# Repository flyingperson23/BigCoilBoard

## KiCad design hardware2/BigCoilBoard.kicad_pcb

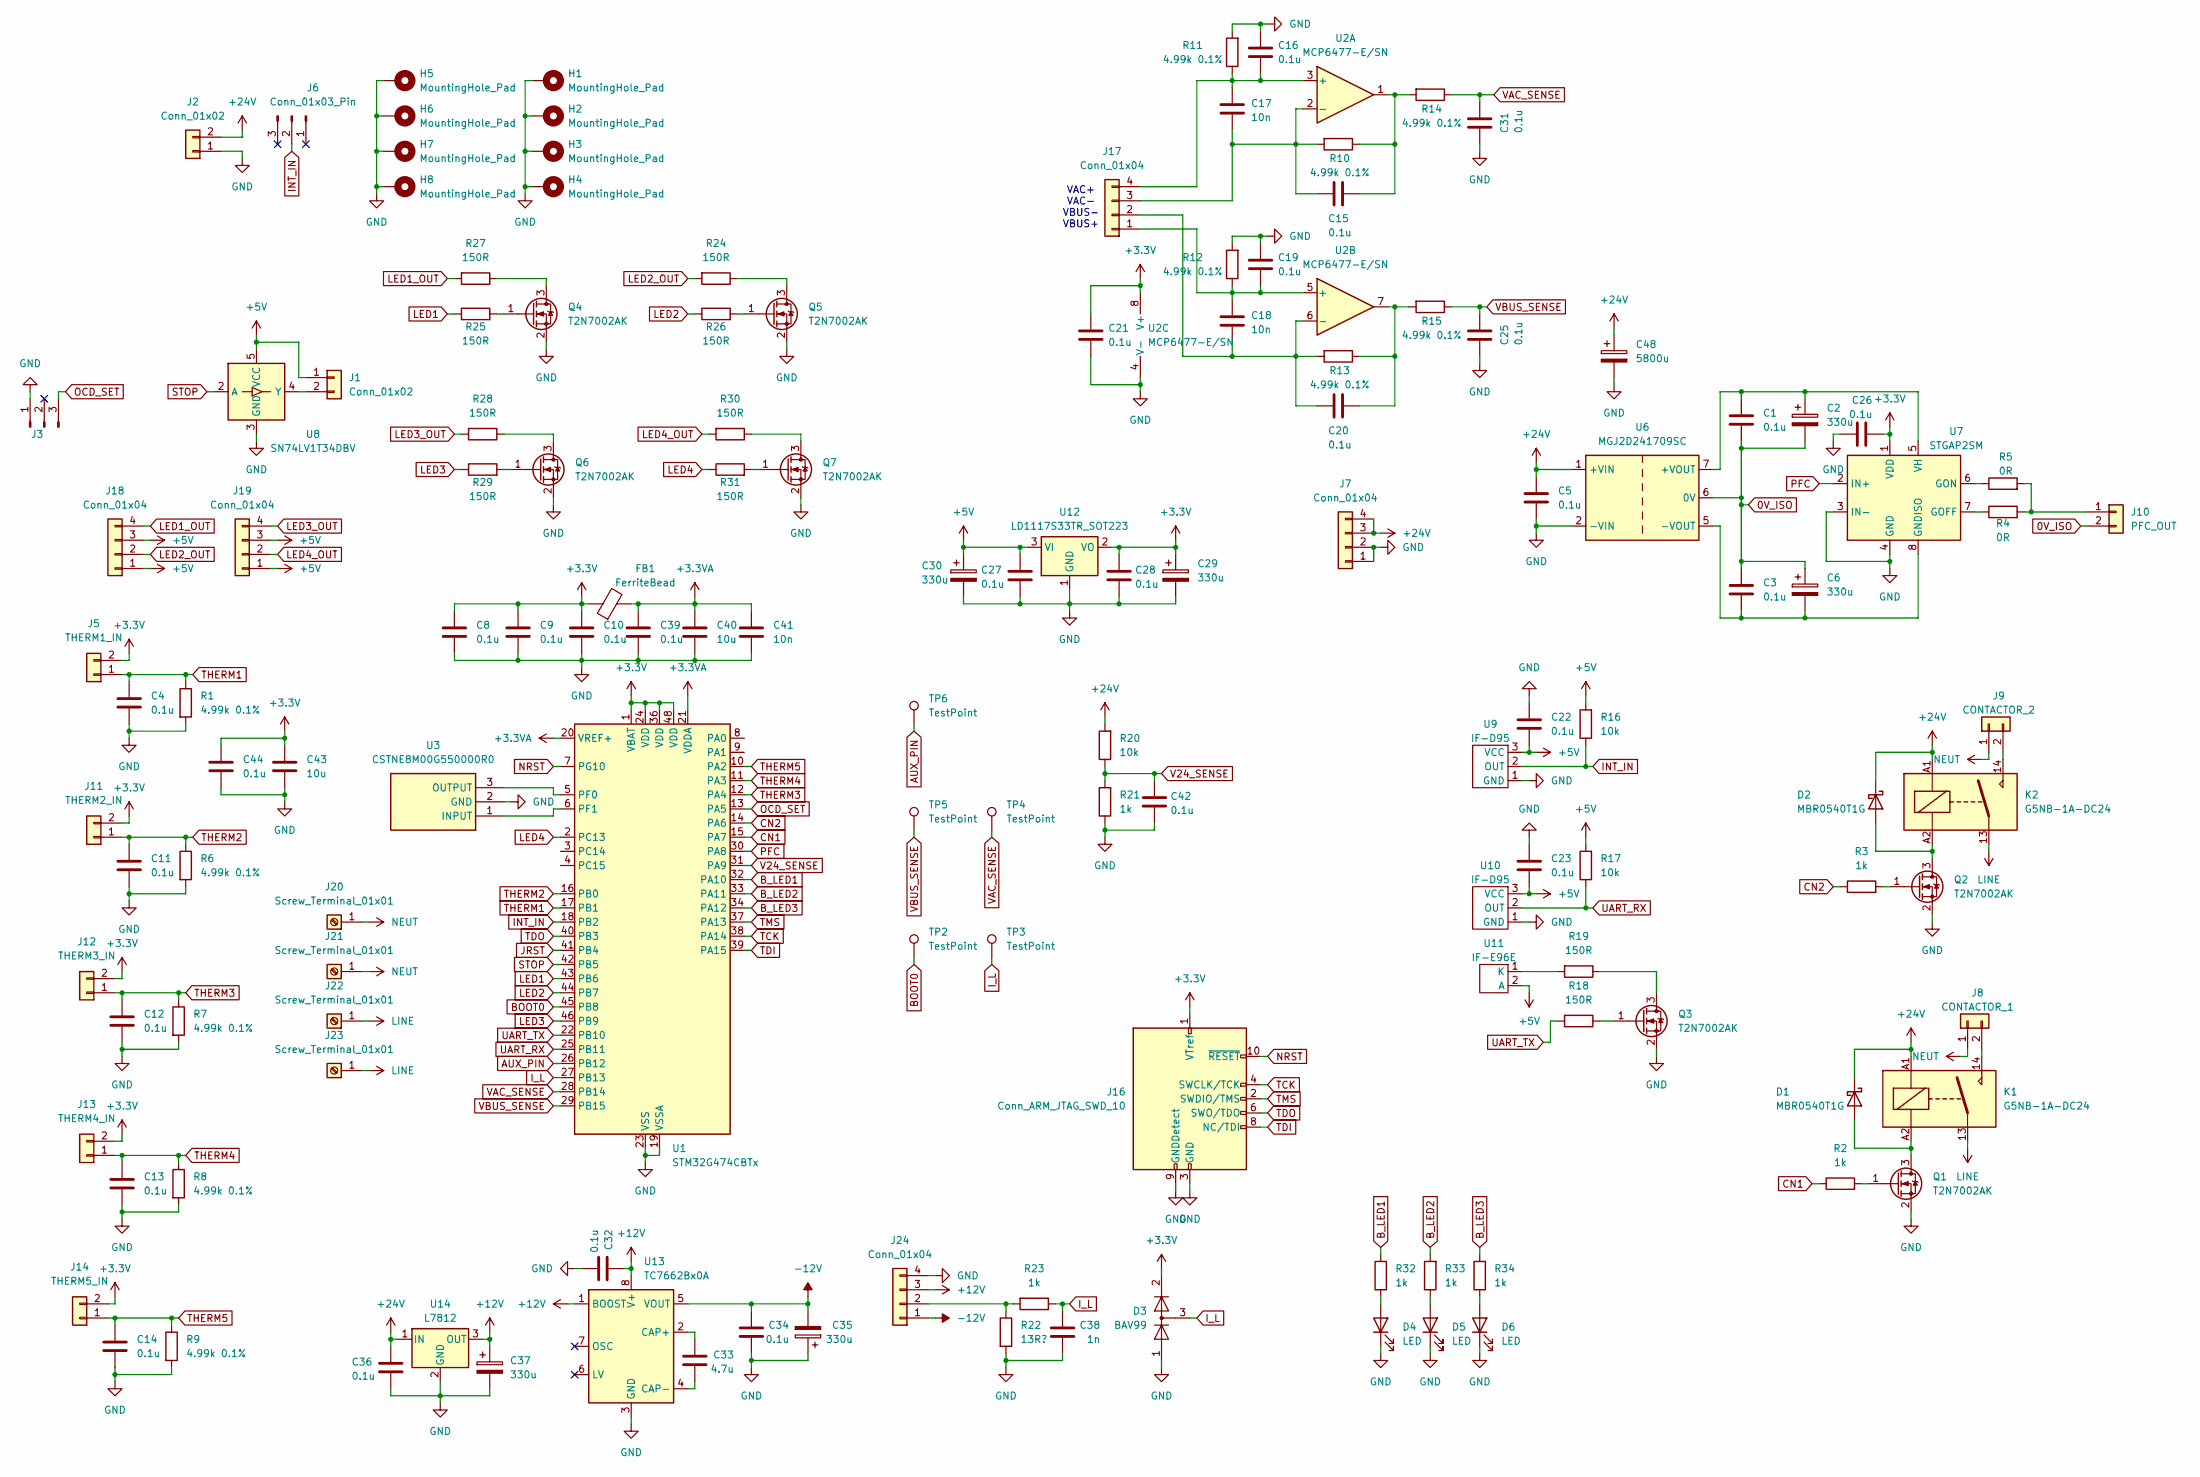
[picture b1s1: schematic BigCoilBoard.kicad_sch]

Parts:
C1, C3, C4, C5, C8, C9, C10, C11, C12, C13, C14, C15, C16, C19, C20, C21, C22, C23, C25, C26, C27, C28, C31, C32, C34, C36, C39, C42, C44: 0.1u; C_0805_2012Metric
C2, C6, C29, C30, C35, C37: 330u; 860020575013
C17, C18, C41: 10n; C_0805_2012Metric
C33: 4.7u; C_0805_2012Metric
C38: 1n; C_0805_2012Metric
C40, C43: 10u; C_0805_2012Metric
C48: 5800u; 860010581026
D1, D2: MBR0540T1G; D_SOD-123
D3: BAV99; SOT-23
D4, D5, D6: LED; LED_0805_2012Metric
FB1: FerriteBead; L_1206_3216Metric
H1, H2, H3, H4: MountingHole_Pad; MountingHole_2.7mm_M2.5_Pad_Via
H5, H6, H7, H8: MountingHole_Pad; MountingHole_4.3mm_M4_Pad_Via
J1, J2: Conn_01x02; PinSocket_1x02_P2.54mm_Vertical
J3, J6: Conn_01x03_Pin; PinSocket_1x03_P2.54mm_Vertical
J5: THERM1_IN; Molex_KK-254_AE-6410-02A_1x02_P2.54mm_Vertical
J7, J17, J18, J19, J24: Conn_01x04; Molex_KK-254_AE-6410-04A_1x04_P2.54mm_Vertical
J8: CONTACTOR_1; Molex_KK-254_AE-6410-02A_1x02_P2.54mm_Vertical
J9: CONTACTOR_2; Molex_KK-254_AE-6410-02A_1x02_P2.54mm_Vertical
J10: PFC_OUT; Molex_KK-254_AE-6410-02A_1x02_P2.54mm_Vertical
J11: THERM2_IN; Molex_KK-254_AE-6410-02A_1x02_P2.54mm_Vertical
J12: THERM3_IN; Molex_KK-254_AE-6410-02A_1x02_P2.54mm_Vertical
J13: THERM4_IN; Molex_KK-254_AE-6410-02A_1x02_P2.54mm_Vertical
J14: THERM5_IN; Molex_KK-254_AE-6410-02A_1x02_P2.54mm_Vertical
J16: Conn_ARM_JTAG_SWD_10; PinHeader_2x05_P1.27mm_Vertical
J20, J21, J22, J23: Screw_Terminal_01x01; Wuerth_REDCUBE-THR_WP-THRBU_74650074_THR
K1, K2: G5NB-1A-DC24; Relay_SPST_Omron_G5NB
Q1, Q2, Q3, Q4, Q5, Q6, Q7: T2N7002AK; SOT-23
R1, R6, R7, R8, R9, R10, R11, R12, R13, R14, R15: 4.99k 0.1%; R_0805_2012Metric
R2, R3, R21, R23, R32, R33, R34: 1k; R_0805_2012Metric
R4, R5: 0R; R_1210_3225Metric
R16, R17, R20: 10k; R_0805_2012Metric
R18, R19, R24, R25, R26, R27, R28, R29, R30, R31: 150R; R_0805_2012Metric
R22: 13R?; R_Axial_DIN0207_L6.3mm_D2.5mm_P10.16mm_Horizontal
TP2, TP3, TP4, TP5, TP6: TestPoint; TestPoint_Pad_2.0x2.0mm
U1: STM32G474CBTx; LQFP-48_7x7mm_P0.5mm
U2: MCP6477-E/SN; SOIC-8_3.9x4.9mm_P1.27mm
U3: CSTNE8M00G550000R0; Resonator_SMD_Murata_CSTxExxV-3Pin_3.0x1.1mm; Mouser Part Number 81-CSTNE8M00G550000R
U6: MGJ2D241709SC; Converter_DCDC_Murata_MGJ2DxxxxxxSC_THT
U7: STGAP2SM; SOIC-8_3.9x4.9mm_P1.27mm
U8: SN74LV1T34DBV; SOT-23-5
U9, U10: IF-D95
U11: IF-E96E
U12: LD1117S33TR_SOT223; SOT-223-3_TabPin2
U13: TC7662Bx0A; SOIC-8_3.9x4.9mm_P1.27mm
U14: L7812; TO-220-3_Vertical

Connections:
0V_ISO: C1.2, C2.2, C3.1, C6.1, J10.2, U6.6 (0V)
+3.3V: C8.1, C9.1, C10.1, C21.1, C26.2, C28.1, C29.1, C43.1, C44.1, D3.2 (A), FB1.1, J5.2, J11.2, J12.2, J13.2, J14.2, J16.1 (VTref), U1.1 (VBAT), U1.24 (VDD), U1.36 (VDD), U1.48 (VDD), U2.8 (V+), U7.1 (VDD), U12.2 (VO)
+3.3VA: C39.1, C40.1, C41.1, FB1.2, U1.20 (VREF+), U1.21 (VDDA)
+5V: C22.2, C23.2, C27.1, C30.1, J1.1, J18.1, J18.3, J19.1, J19.3, R16.2, R17.2, U8.5 (VCC), U9.3 (VCC), U10.3 (VCC), U11.2 (A), U12.3 (VI)
+12V: C32.1, C37.1, J24.3, U13.1 (BOOST), U13.8 (V+), U14.3 (OUT)
+24V: C5.1, C36.1, C48.1, D1.1 (K), D2.1 (K), J2.2, J7.3, J7.4, K1.A1, K2.A1, R20.2, U6.1 (+VIN), U14.1 (IN)
-12V: C34.2, C35.2, J24.1, U13.5 (VOUT)
AUX_PIN: TP6.1, U1.26 (PB12)
BOOT0: TP2.1, U1.45 (PB8)
B_LED1: R32.2, U1.32 (PA10)
B_LED2: R33.2, U1.33 (PA11)
B_LED3: R34.2, U1.34 (PA12)
CN1: R2.1, U1.15 (PA7)
CN2: R3.1, U1.14 (PA6)
GND: C4.2, C5.2, C8.2, C9.2, C10.2, C11.2, C12.2, C13.2, C14.2, C16.1, C19.1, C21.2, C22.1, C23.1, C25.2, C26.1, C27.2, C28.2, C29.2, C30.2, C31.2, C32.2, C34.1, C35.1, C36.2, C37.2, C38.1, C39.2, C40.2, C41.2, C42.2, C43.2, C44.2, C48.2, D3.1 (K), D4.1 (K), D5.1 (K), D6.1 (K), H1.1, H2.1, H3.1, H4.1, H5.1, H6.1, H7.1, H8.1, J2.1, J3.1, J7.1, J7.2, J16.3 (GND), J16.5 (GND), J16.9 (GNDDetect), J24.4, Q1.2 (S), Q2.2 (S), Q3.2 (S), Q4.2 (S), Q5.2 (S), Q6.2 (S), Q7.2 (S), R1.2, R6.2, R7.2, R8.2, R9.2, R11.2, R12.2, R21.1, R22.2, U1.19 (VSSA), U1.23 (VSS), U1.35 (VSS), U1.47 (VSS), U2.4 (V-), U3.2 (GND), U6.2 (-VIN), U7.3 (IN-), U7.4 (GND), U8.3 (GND), U9.1 (GND), U10.1 (GND), U12.1 (GND), U13.3 (GND), U14.2 (GND)
INT_IN: J6.2, R16.1, U1.18 (PB2), U9.2 (OUT)
I_L: C38.2, D3.3 (K), R23.1, TP3.1, U1.27 (PB13)
JRST: U1.41 (PB4)
LED1: R25.1, U1.43 (PB6)
LED1_OUT: J18.4, R27.2
LED2: R26.1, U1.44 (PB7)
LED2_OUT: J18.2, R24.2
LED3: R29.1, U1.46 (PB9)
LED3_OUT: J19.4, R28.2
LED4: R31.1, U1.2 (PC13)
LED4_OUT: J19.2, R30.2
LINE: J22.1, J23.1, K1.13, K2.13
NEUT: J8.1, J9.1, J20.1, J21.1
NRST: J16.10 (~RESET), U1.7 (PG10)
unnamed: C15.1, R10.1, R14.2, U2.1
unnamed: C20.1, R13.1, R15.2, U2.7
unnamed: D1.2 (A), K1.A2, Q1.3 (D)
unnamed: D2.2 (A), K2.A2, Q2.3 (D)
unnamed: D4.2 (A), R32.1
unnamed: D5.2 (A), R33.1
unnamed: D6.2 (A), R34.1
unnamed: J1.2, U8.4 (Y)
unnamed: J8.2, K1.14
unnamed: J9.2, K2.14
unnamed: J10.1, R4.2, R5.2
unnamed: C18.1, C19.2, J17.1, R12.1, U2.5 (+)
unnamed: C18.2, C20.2, J17.2, R13.2, U2.6 (-)
unnamed: C15.2, C17.2, J17.3, R10.2, U2.2 (-)
unnamed: C16.2, C17.1, J17.4, R11.1, U2.3 (+)
unnamed: J24.2, R22.1, R23.2
unnamed: Q1.1 (G), R2.2
unnamed: Q2.1 (G), R3.2
unnamed: Q3.3 (D), R19.1
unnamed: Q3.1 (G), R18.1
unnamed: Q4.3 (D), R27.1
unnamed: Q4.1 (G), R25.2
unnamed: Q5.3 (D), R24.1
unnamed: Q5.1 (G), R26.2
unnamed: Q6.3 (D), R28.1
unnamed: Q6.1 (G), R29.2
unnamed: Q7.3 (D), R30.1
unnamed: Q7.1 (G), R31.2
unnamed: U1.5 (PF0), U3.3 (OUTPUT)
unnamed: U1.6 (PF1), U3.1 (INPUT)
unnamed: C1.1, C2.1, U6.7 (+VOUT), U7.5 (VH)
unnamed: C3.2, C6.2, U6.5 (-VOUT), U7.8 (GNDISO)
unnamed: R4.1, U7.7 (GOFF)
unnamed: R5.1, U7.6 (GON)
unnamed: R19.2, U11.1 (K)
unnamed: C33.2, U13.2 (CAP+)
unnamed: C33.1, U13.4 (CAP-)
OCD_SET: J3.3, U1.13 (PA5)
PFC: U1.30 (PA8), U7.2 (IN+)
STOP: U1.42 (PB5), U8.2 (A)
TCK: J16.4 (SWCLK/TCK), U1.38 (PA14)
TDI: J16.8 (NC/TDI), U1.39 (PA15)
TDO: J16.6 (SWO/TDO), U1.40 (PB3)
THERM1: C4.1, J5.1, R1.1, U1.17 (PB1)
THERM2: C11.1, J11.1, R6.1, U1.16 (PB0)
THERM3: C12.1, J12.1, R7.1, U1.12 (PA4)
THERM4: C13.1, J13.1, R8.1, U1.11 (PA3)
THERM5: C14.1, J14.1, R9.1, U1.10 (PA2)
TMS: J16.2 (SWDIO/TMS), U1.37 (PA13)
UART_RX: R17.1, U1.25 (PB11), U10.2 (OUT)
UART_TX: R18.2, U1.22 (PB10)
V24_SENSE: C42.1, R20.1, R21.2, U1.31 (PA9)
VAC_SENSE: C31.1, R14.1, TP4.1, U1.28 (PB14)
VBUS_SENSE: C25.1, R15.1, TP5.1, U1.29 (PB15)

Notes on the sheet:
VAC+ VAC- VBUS- VBUS+

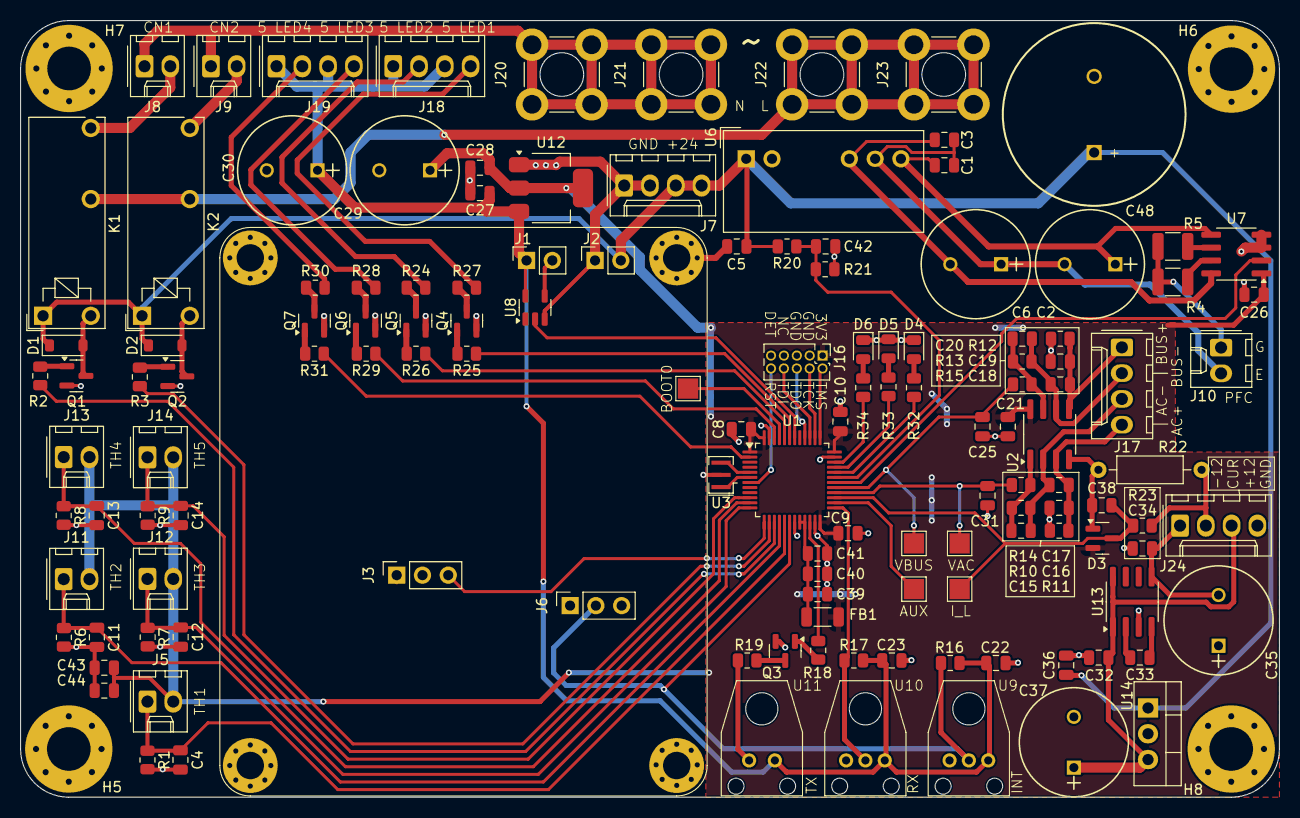
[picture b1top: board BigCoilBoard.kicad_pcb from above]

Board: 2 copper layers, 124.0 x 76.5 mm, 140 parts (0 on the bottom side), 82 nets.

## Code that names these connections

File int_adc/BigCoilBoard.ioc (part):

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Mcu.Name=STM32G474C(B-C-E)Tx
Mcu.Package=LQFP48
Mcu.UserName=STM32G474CBTx
PA10.GPIOParameters=GPIO_Label
PA10.GPIO_Label=BLED1
PA10.Signal=GPIO_Output
PA11.GPIOParameters=GPIO_Label
PA11.GPIO_Label=BLED2
PA11.Signal=GPIO_Output
PA12.GPIOParameters=GPIO_Label
PA12.GPIO_Label=BLED3
PA12.Signal=GPIO_Output
PA13.Mode=JTAG_4_pins
PA13.Signal=SYS_JTMS-SWDIO
PA14.Mode=JTAG_4_pins
PA14.Signal=SYS_JTCK-SWCLK
PA15.Mode=JTAG_4_pins
PA15.Signal=SYS_JTDI
PA2.GPIOParameters=GPIO_Label
PA2.GPIO_Label=THERM5
PA2.Mode=IN3-Single-Ended
PA2.Signal=ADC1_IN3
PA3.GPIOParameters=GPIO_Label
PA3.GPIO_Label=THERM4
PA3.Mode=IN4-Single-Ended
PA3.Signal=ADC1_IN4
PA4.GPIOParameters=GPIO_Label
PA4.GPIO_Label=THERM3
PA4.Mode=IN17-Single-Ended
PA4.Signal=ADC2_IN17
PA5.GPIOParameters=GPIO_Label
PA5.GPIO_Label=OCD_OUT
PA5.Signal=COMP_DAC12_group
PA6.GPIOParameters=GPIO_Label
PA6.GPIO_Label=CN2
PA6.Signal=GPIO_Output
PA7.GPIOParameters=GPIO_Label
PA7.GPIO_Label=CN1
PA7.Signal=GPIO_Output
PA8.GPIOParameters=GPIO_Label
PA8.GPIO_Label=PFC
PA8.Signal=S_TIM1_CH1
PA9.GPIOParameters=GPIO_Label
PA9.GPIO_Label=V24_SENSE
PA9.Mode=IN2-Single-Ended
PA9.Signal=ADC5_IN2
PB0.GPIOParameters=GPIO_Label
PB0.GPIO_Label=THERM2
PB0.Mode=IN15-Single-Ended
PB0.Signal=ADC1_IN15
PB1.GPIOParameters=GPIO_Label
PB1.GPIO_Label=THERM1
PB1.Mode=IN12-Single-Ended
PB1.Signal=ADC1_IN12
PB10.Mode=Asynchronous
PB10.Signal=USART3_TX
PB11.Mode=Asynchronous
PB11.Signal=USART3_RX
PB13.GPIOParameters=GPIO_Label
PB13.GPIO_Label=I_L_SENSE
PB13.Signal=SharedAnalog_PB13
PB14.GPIOParameters=GPIO_Label
PB14.GPIO_Label=VAC_SENSE
PB14.Mode=IN4-Single-Ended
PB14.Signal=ADC4_IN4
PB15.GPIOParameters=GPIO_Label
PB15.GPIO_Label=VBUS_SENSE
PB15.Mode=IN5-Single-Ended
PB15.Signal=ADC4_IN5
PB2.GPIOParameters=GPIO_Label
PB2.GPIO_Label=INT_IN
PB2.Signal=GPXTI2
PB3.Mode=JTAG_4_pins
PB3.Signal=SYS_JTDO-SWO
PB4.Signal=SYS_JTRST
PB5.GPIOParameters=GPIO_Label
PB5.GPIO_Label=STOP
PB5.Signal=GPIO_Output
PB6.GPIOParameters=GPIO_Label
PB6.GPIO_Label=LED1
PB6.Signal=GPIO_Output
PB7.GPIOParameters=GPIO_Label
PB7.GPIO_Label=LED2
PB7.Signal=GPIO_Output
PB9.GPIOParameters=GPIO_Label
PB9.GPIO_Label=LED3
PB9.Signal=GPIO_Output
PC13.GPIOParameters=GPIO_Label
PC13.GPIO_Label=LED4
PC13.Signal=GPIO_Output
PF0-OSC_IN.Mode=HSE-External-Oscillator
PF0-OSC_IN.Signal=RCC_OSC_IN
PF1-OSC_OUT.Mode=HSE-External-Oscillator
PF1-OSC_OUT.Signal=RCC_OSC_OUT
RCC.HSE_VALUE=8000000
RCC.SYSCLKFreq_VALUE=170000000
RCC.SYSCLKSource=RCC_SYSCLKSOURCE_PLLCLK
board=custom

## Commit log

2025-02-18 Create hardware
2025-02-25 austins stuff
2025-03-05 actually works ???
2025-03-11 internal adc software
2025-04-02 back to int adc
2025-10-01 v3 work, implemented dcm pfc in v2
2026-04-08 working for cpw 26
2026-04-09 slow down vbus rampup
